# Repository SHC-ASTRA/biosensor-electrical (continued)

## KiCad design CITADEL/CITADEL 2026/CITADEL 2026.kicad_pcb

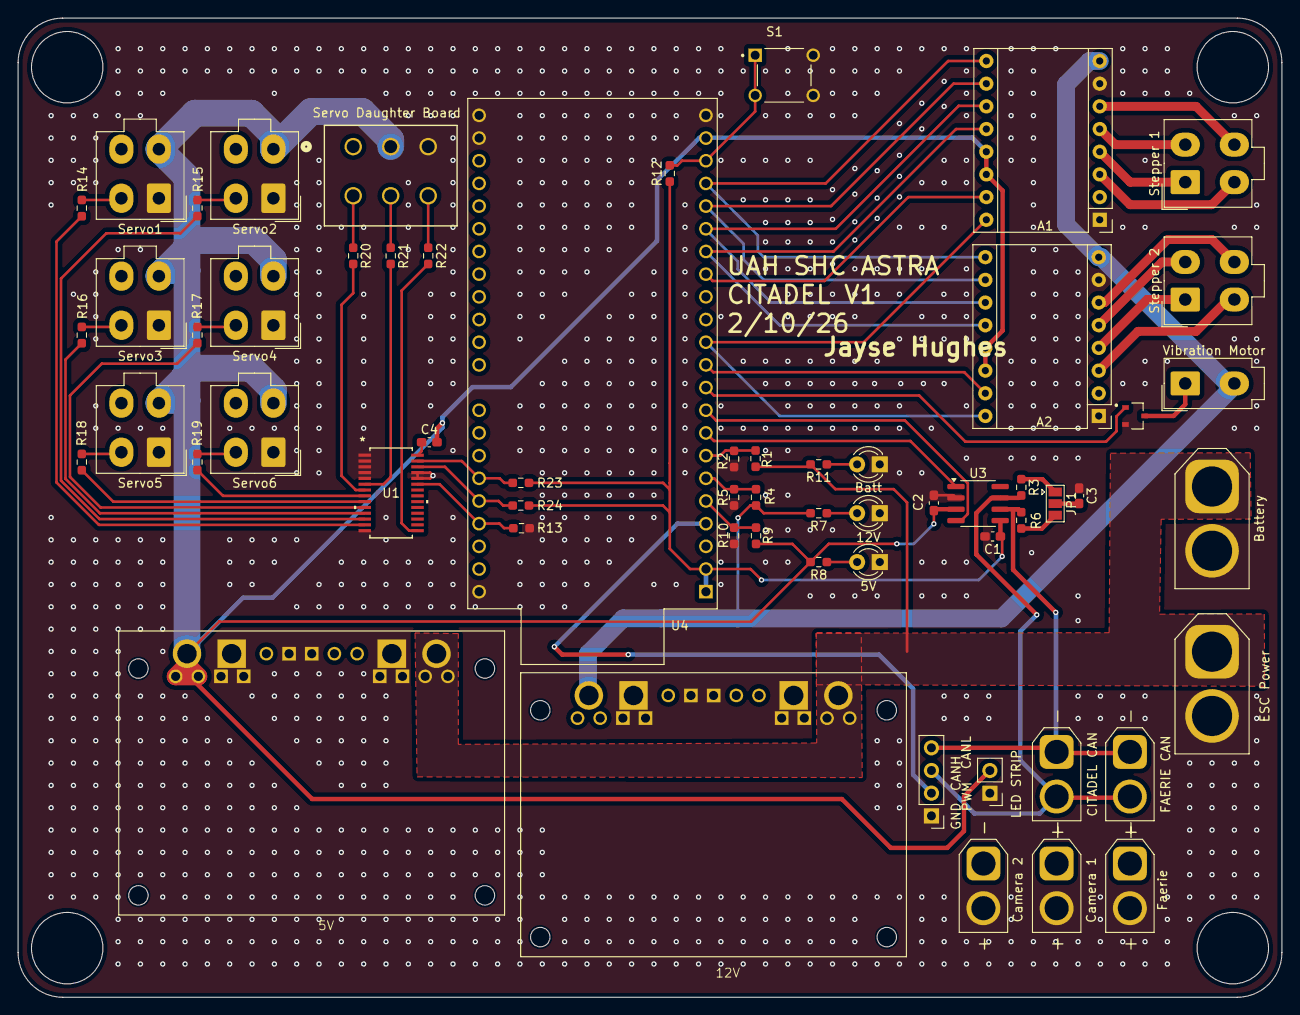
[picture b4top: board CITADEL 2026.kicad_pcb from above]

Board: 2 copper layers, 141.5 x 109.7 mm, 60 parts (0 on the bottom side), 59 nets.

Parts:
5V, 12V: LED; LED_D3.0mm
5V#2: PS1; D24V15OF5
12V#2: PS2; D24V15OF5
A1, A2: Pololu_Breakout_DRV8825; Pololu_Breakout-16_15.2x20.3mm
Batt: LED; LED_D3.0mm
Battery: Battery Connections; AMASS_XT60-M_1x02_P7.20mm_Vertical
C1, C2, C3: C; C_0603_1608Metric_Pad1.08x0.95mm_HandSolder
C4: 10uF; C_0603_1608Metric_Pad1.08x0.95mm_HandSolder
CITADEL CAN: CAN BUS; AMASS_XT30U-M_1x02_P5.0mm_Vertical
Camera 1: Camera 1; AMASS_XT30U-M_1x02_P5.0mm_Vertical
Camera 2: Camera 2; AMASS_XT30U-M_1x02_P5.0mm_Vertical
ESC Power: ESC PWR; AMASS_XT60-M_1x02_P7.20mm_Vertical
FAERIE CAN: Faerie CAN BUS; AMASS_XT30U-M_1x02_P5.0mm_Vertical
Faerie: Faerie; AMASS_XT30U-M_1x02_P5.0mm_Vertical
GND: ESC Comms; PinHeader_1x04_P2.54mm_Vertical
JP1: SolderJumper_3_Open; SolderJumper-3_P1.3mm_Open_Pad1.0x1.5mm
LED STRIP: LED Strip; PinHeader_1x02_P2.54mm_Vertical
Q7: SSM3K329R_LF; SSM3K329_LF
R1, R4, R9, R10, R12: 10 kΩ; R_0603_1608Metric_Pad0.98x0.95mm_HandSolder
R2: 2.21 kΩ; R_0603_1608Metric_Pad0.98x0.95mm_HandSolder
R3, R6: R_US; R_0603_1608Metric_Pad0.98x0.95mm_HandSolder
R5: 3.32 kΩ; R_0603_1608Metric_Pad0.98x0.95mm_HandSolder
R7, R8, R11: 1000; R_0603_1608Metric_Pad0.98x0.95mm_HandSolder
R13: 10kΩ; R_0603_1608Metric_Pad0.98x0.95mm_HandSolder
R14, R15, R16, R17, R18, R19, R20, R21, R22: 220Ω; R_0603_1608Metric_Pad0.98x0.95mm_HandSolder
R23, R24: 4.7 kΩ; R_0603_1608Metric_Pad0.98x0.95mm_HandSolder
S1: Push Button; SW_TS02-66-60-BK-100-SCR-D
Servo1: MG90S 1; Molex_Mini-Fit_Jr_5566-04A_2x02_P4.20mm_Vertical
Servo2: MG90S 2; Molex_Mini-Fit_Jr_5566-04A_2x02_P4.20mm_Vertical
Servo3: MG90S 3; Molex_Mini-Fit_Jr_5566-04A_2x02_P4.20mm_Vertical
Servo4: MG90S 4; Molex_Mini-Fit_Jr_5566-04A_2x02_P4.20mm_Vertical
Servo5: MG90S 5; Molex_Mini-Fit_Jr_5566-04A_2x02_P4.20mm_Vertical
Servo6: MG90S 6; Molex_Mini-Fit_Jr_5566-04A_2x02_P4.20mm_Vertical
Servo Daughter Board: Servo_Daughter; CONN_SD-5566-002_06_MOL
Stepper 1: Stepper 1; Molex_Mini-Fit_Jr_5566-04A_2x02_P4.20mm_Vertical
Stepper 2: Stepper 2; Molex_Mini-Fit_Jr_5566-04A_2x02_P4.20mm_Vertical
U1: PCA9685PW_118; TSSOP28_SOT361-1_NXP
U3: TJA1051T-3; SOIC-8_3.9x4.9mm_P1.27mm
U4: ESP32-S3-DEVKITC-1-N8R8
Vibration Motor: Vibration Motor; Molex_Mini-Fit_Jr_5566-02A_2x01_P4.20mm_Vertical

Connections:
+3.3V: C1.1, R12.1, R23.2, R24.2, U3.5 (VIO), U4.J1_1 (3V3), U4.J1_2 (3V3.)
+5V: 5V#2.VOUT, 5V#2.VOUT_1 (VOUT), 5V#2.VOUT_2 (VOUT), A1.13 (~RST), A1.14 (~SLP), A2.13 (~RST), A2.14 (~SLP), C2.2, C4.2, LED STRIP.2, R8.2, R9.1, Servo1.3 (+), Servo2.3 (+), Servo3.3 (+), Servo4.3 (+), Servo5.3 (+), Servo6.3 (+), Servo Daughter Board.2, U3.3 (VCC), U4.J1_21 (5V0)
+12V: 12V#2.VOUT, 12V#2.VOUT_1 (VOUT), 12V#2.VOUT_2 (VOUT), A1.8 (VMOT), A2.8 (VMOT), Camera 1.1, Camera 2.1, Faerie.1, R4.1, R7.2, Vibration Motor.2
+BATT: 5V#2.VIN, 5V#2.VIN_1 (VIN), 5V#2.VIN_2 (VIN), 12V#2.VIN, 12V#2.VIN_1 (VIN), 12V#2.VIN_2 (VIN), Battery.1, ESC Power.1, R1.1, R11.2
/5V_ADC: R9.2, R10.1, U4.J1_5 (GPIO5)
/12V_ADC: R4.2, R5.1, U4.J1_6 (GPIO6)
/BATT_ADC: R1.2, R2.1, U4.J1_7 (GPIO7)
/Button: R12.2, S1.1, S1.3, U4.J1_20 (GPIO14)
/CIT_CAN+: CITADEL CAN.2, FAERIE CAN.2, GND.3, R3.2, U3.7 (CANH)
/CIT_CAN-: CITADEL CAN.1, FAERIE CAN.1, GND.4, R6.2, U3.6 (CANL)
/CRX_ESP: U3.4 (RXD), U4.J1_9 (GPIO16)
/CTX_ESP: U3.1 (TXD), U4.J1_8 (GPIO15)
/ESC_PWM: GND.2, U4.J1_4 (GPIO4)
/Motor1_1: A1.4 (A1), Stepper 1.1
/Motor1_2: A1.3 (A2), Stepper 1.3
/Motor1_3: A1.5 (B1), Stepper 1.2
/Motor1_4: A1.6 (B2), Stepper 1.4
/Motor2_1: A2.4 (A1), Stepper 2.1
/Motor2_2: A2.3 (A2), Stepper 2.3
/Motor2_3: A2.5 (B1), Stepper 2.2
/Motor2_4: A2.6 (B2), Stepper 2.4
/SCL: R24.1, U1.26 (SCL), U4.J3_5 (GPIO2)
/SDA: R23.1, U1.27 (SDA), U4.J3_6 (MTMS/GPIO42)
/Servo1: R14.1, Servo1.2 (PWM)
/Servo2: R15.1, Servo2.2 (PWM)
/Servo3: R16.1, Servo3.2 (PWM)
/Servo4: R17.1, Servo4.2 (PWM)
/Servo5: R18.1, Servo5.2 (PWM)
/Servo6: R19.1, Servo6.2 (PWM)
/Servo7: R20.1, Servo Daughter Board.4
/Servo8: R21.1, Servo Daughter Board.5
/Servo9: R22.2, Servo Daughter Board.6
/Servo_Enable_Output: R13.1, U1.23 (*OE), U4.J3_4 (GPIO1)
/Stepper1_STEP: A1.15 (STEP), U4.J1_15 (GPIO9)
/Stepper2_STEP: A2.15 (STEP), U4.J1_11 (GPIO18)
/Stepper_DIR: A1.16 (DIR), A2.16 (DIR), U4.J1_12 (GPIO8)
/Stepper_EN: A1.9 (~EN), A2.9 (~EN), U4.J1_19 (GPIO13)
/Stepper_M0: A1.10 (M0), A2.10 (M0), U4.J1_18 (GPIO12)
/Stepper_M1: A1.11 (M1), A2.11 (M1), U4.J1_17 (GPIO11)
/Stepper_M2: A1.12 (M2), A2.12 (M2), U4.J1_16 (GPIO10)
/VibMotorMOS: Q7.3, Vibration Motor.1
/VibMotorSignal: Q7.1, U4.J1_10 (GPIO17)
GND: 5V.1 (K), 5V#2.GND, 5V#2.GND1 (GND), 5V#2.GND2 (GND), 5V#2.GND3 (GND), 5V#2.GND4 (GND), 5V#2.GND5 (GND), 5V#2.GND6 (GND), 5V#2.GND7 (GND), 12V.1 (K), 12V#2.GND, 12V#2.GND1 (GND), 12V#2.GND2 (GND), 12V#2.GND3 (GND), 12V#2.GND4 (GND), 12V#2.GND5 (GND), 12V#2.GND6 (GND), 12V#2.GND7 (GND), A1.1 (GND), A1.7 (GND), A2.1 (GND), A2.7 (GND), Batt.1 (K), Battery.2, C1.2, C2.1, C3.1, Camera 1.2, Camera 2.2, ESC Power.2, Faerie.2, GND.1, LED STRIP.1, Q7.2, R2.2, R5.2, R10.2, R13.2, S1.2, S1.4, Servo1.1 (-), Servo2.1 (-), Servo3.1 (-), Servo4.1 (-), Servo5.1 (-), Servo6.1 (-), Servo Daughter Board.3, U1.1 (A0), U1.2 (A1), U1.3 (A2), U1.4 (A3), U1.5 (A4), U1.14 (VSS), U1.24 (A5), U1.25 (EXTCLK), U3.2 (GND), U4.J1_22 (GND3), U4.J3_1 (GND), U4.J3_21 (GND1), U4.J3_22 (GND2)
unnamed: Batt.2 (A), R11.1
unnamed: 12V.2 (A), R7.1
unnamed: 5V.2 (A), R8.1
unnamed: JP1.3 (A), R6.1
unnamed: JP1.1 (B), R3.1
unnamed: C3.2, JP1.2 (C)
unnamed: R21.2, U1.6 (LED0)
unnamed: R20.2, U1.7 (LED1)
unnamed: R19.2, U1.8 (LED2)
unnamed: R18.2, U1.9 (LED3)
unnamed: R17.2, U1.10 (LED4)
unnamed: R16.2, U1.11 (LED5)
unnamed: R15.2, U1.12 (LED6)
unnamed: R14.2, U1.13 (LED7)
unnamed: R22.1, U1.15 (LED8)
unnamed: C4.1, U1.28 (VDD)

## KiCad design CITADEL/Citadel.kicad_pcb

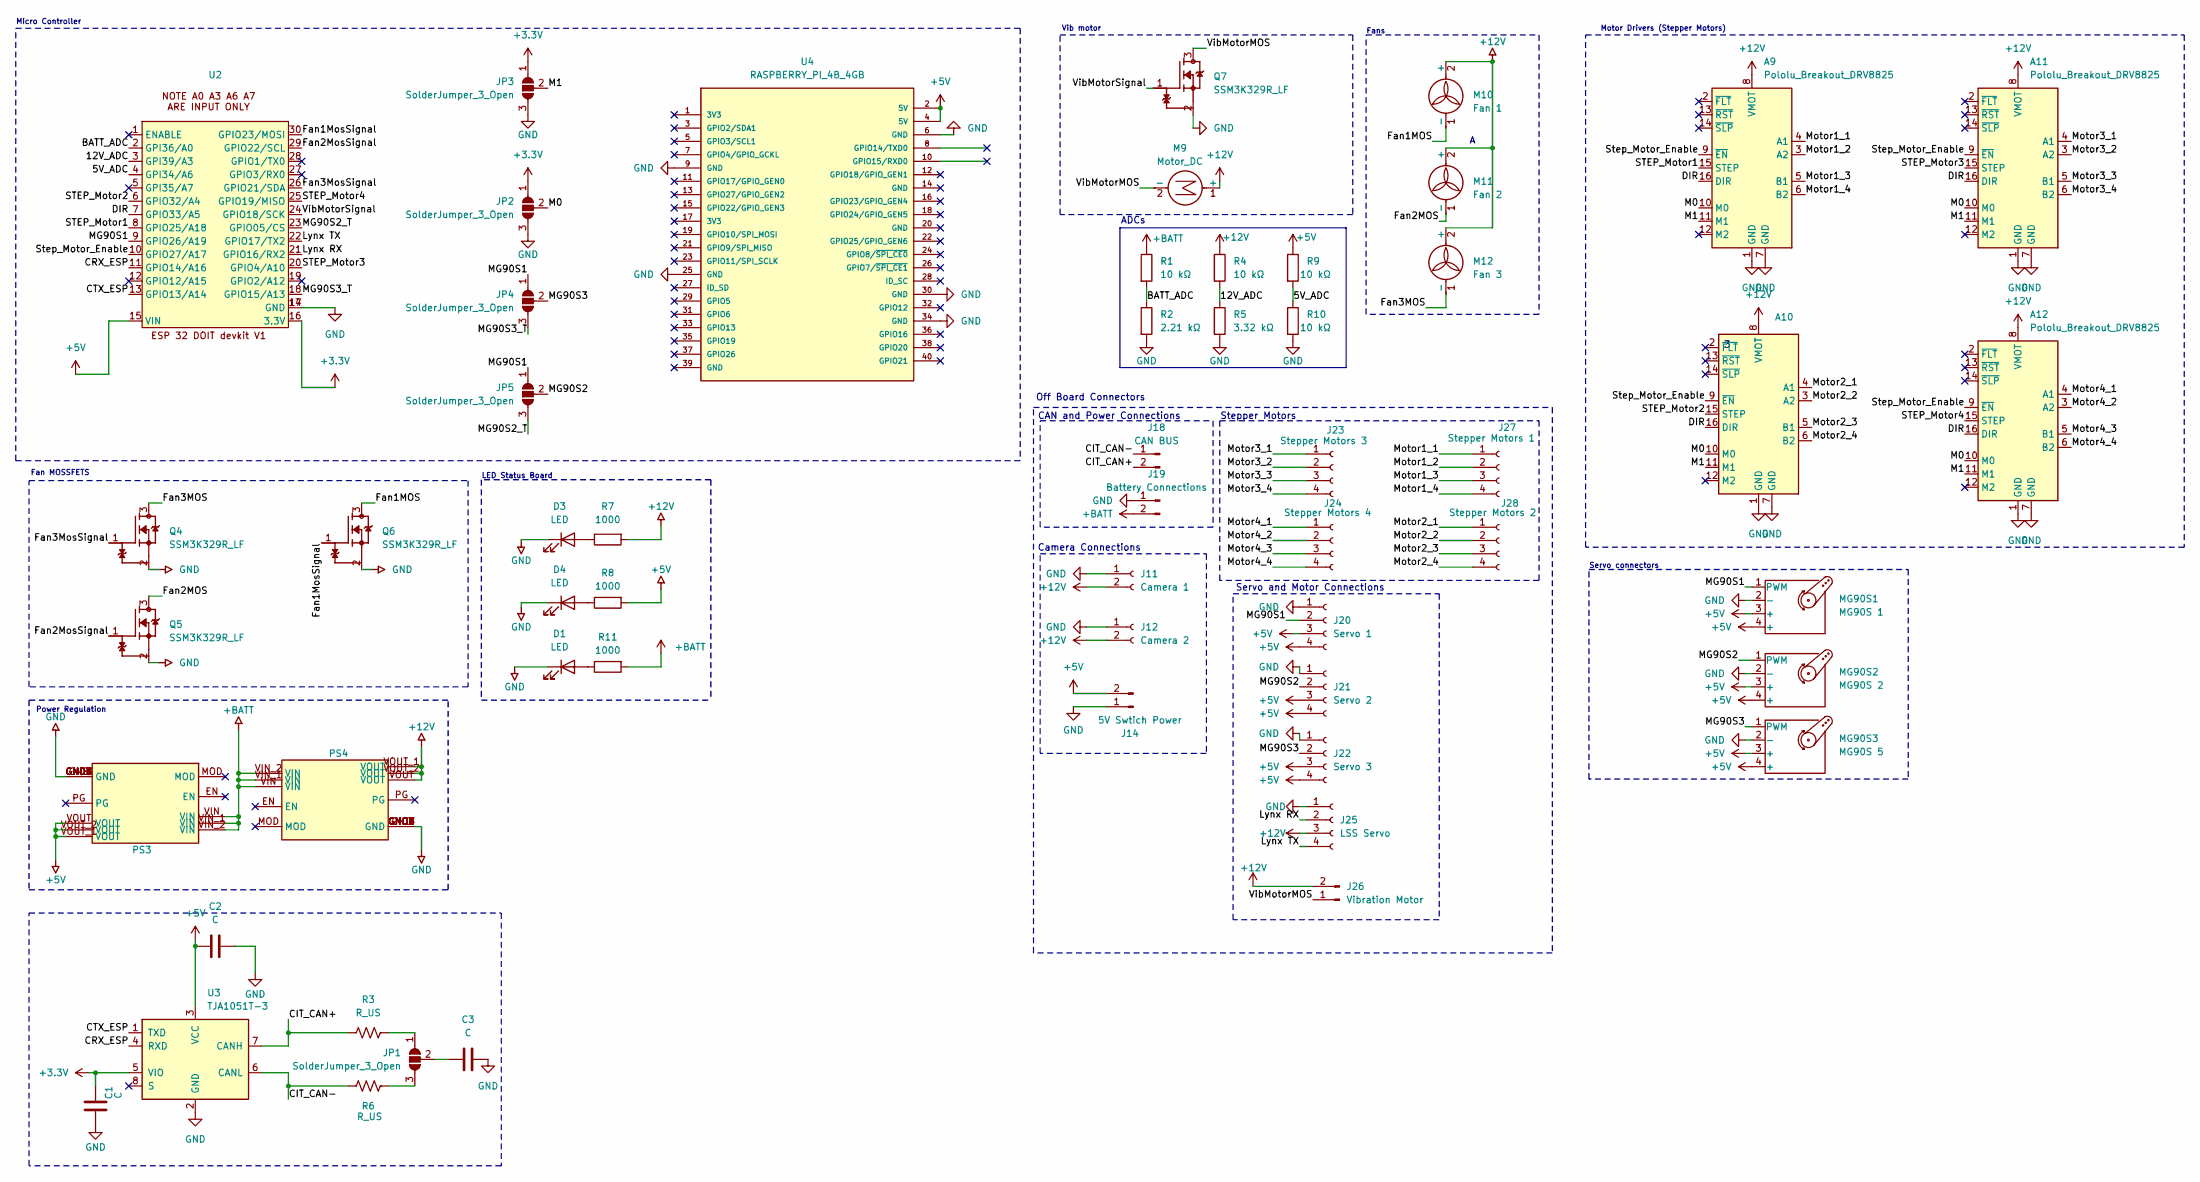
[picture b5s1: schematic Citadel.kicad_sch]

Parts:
A9, A10, A11, A12: Pololu_Breakout_DRV8825; Pololu_Breakout-16_15.2x20.3mm
C1, C2, C3: C; C_0603_1608Metric_Pad1.08x0.95mm_HandSolder
D1, D3, D4: LED; LED_D3.0mm
J11: Camera 1; AMASS_XT30U-F_1x02_P5.0mm_Vertical
J12: Camera 2; AMASS_XT30U-F_1x02_P5.0mm_Vertical
J14: 5V Swtich Power; Molex_Mini-Fit_Jr_5566-02A_2x01_P4.20mm_Vertical
J18: CAN BUS; AMASS_XT30U-F_1x02_P5.0mm_Vertical
J19: Battery Connections; AMASS_XT60-M_1x02_P7.20mm_Vertical
J20: Servo 1; Molex_Mini-Fit_Jr_5566-04A_2x02_P4.20mm_Vertical
J21: Servo 2; Molex_Mini-Fit_Jr_5566-04A_2x02_P4.20mm_Vertical
J22: Servo 3; Molex_Mini-Fit_Jr_5566-04A_2x02_P4.20mm_Vertical
J23: Stepper Motors 3; Molex_Mini-Fit_Jr_5566-04A_2x02_P4.20mm_Vertical
J24: Stepper Motors 4; Molex_Mini-Fit_Jr_5566-04A_2x02_P4.20mm_Vertical
J25: LSS Servo; Molex_Mini-Fit_Jr_5566-04A_2x02_P4.20mm_Vertical
J26: Vibration Motor; Molex_Mini-Fit_Jr_5566-02A_2x01_P4.20mm_Vertical
J27: Stepper Motors 1; Molex_Mini-Fit_Jr_5566-04A_2x02_P4.20mm_Vertical
J28: Stepper Motors 2; Molex_Mini-Fit_Jr_5566-04A_2x02_P4.20mm_Vertical
JP1, JP2, JP3, JP4, JP5: SolderJumper_3_Open; SolderJumper-3_P1.3mm_Open_Pad1.0x1.5mm
M9: Motor_DC
M10: Fan 1; Molex_Mini-Fit_Jr_5566-02A_2x01_P4.20mm_Vertical
M11: Fan 2; Molex_Mini-Fit_Jr_5566-02A_2x01_P4.20mm_Vertical
M12: Fan 3; Molex_Mini-Fit_Jr_5566-02A_2x01_P4.20mm_Vertical
MG90S1: MG90S 1
MG90S2: MG90S 2
MG90S3: MG90S 5
PS3, PS4: D24V15OF5
Q4, Q5, Q6, Q7: SSM3K329R_LF; SSM3K329_LF; PARTREV 1.0
R1, R4, R9, R10: 10 kΩ; R_0603_1608Metric_Pad0.98x0.95mm_HandSolder
R2: 2.21 kΩ; R_0603_1608Metric_Pad0.98x0.95mm_HandSolder
R3, R6: R_US; R_0603_1608Metric_Pad0.98x0.95mm_HandSolder
R5: 3.32 kΩ; R_0603_1608Metric_Pad0.98x0.95mm_HandSolder
R7, R8, R11: 1000; R_0603_1608Metric_Pad0.98x0.95mm_HandSolder
U2: esp32_devkit_v1
U3: TJA1051T-3; SOIC-8_3.9x4.9mm_P1.27mm
U4: RASPBERRY_PI_4B_4GB; MODULE_RASPBERRY_PI_4B_4GB

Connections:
+3.3V: C1.1, JP2.1 (B), JP3.1 (B), U2.16 (3.3V), U3.5 (VIO)
+5V: C2.2, J14.2, J20.3, J20.4, J21.3, J21.4, J22.3, J22.4, MG90S1.3 (+), MG90S1.4 (+), MG90S2.3 (+), MG90S2.4 (+), MG90S3.3 (+), MG90S3.4 (+), PS3.VOUT, PS3.VOUT_1 (VOUT), PS3.VOUT_2 (VOUT), R8.2, R9.1, U2.15 (VIN), U3.3 (VCC), U4.2 (5V), U4.4 (5V)
+12V: A9.8 (VMOT), A10.8 (VMOT), A11.8 (VMOT), A12.8 (VMOT), J11.2, J12.2, J25.3, J26.2, M9.1 (+), M10.2 (+), M11.2 (+), M12.2 (+), PS4.VOUT, PS4.VOUT_1 (VOUT), PS4.VOUT_2 (VOUT), R4.1, R7.2
+BATT: J19.2, PS3.VIN, PS3.VIN_1 (VIN), PS3.VIN_2 (VIN), PS4.VIN, PS4.VIN_1 (VIN), PS4.VIN_2 (VIN), R1.1, R11.2
/5V_ADC: R9.2, R10.1, U2.4 (GPI34/A6)
/12V_ADC: R4.2, R5.1, U2.3 (GPI39/A3)
/BATT_ADC: R1.2, R2.1, U2.2 (GPI36/A0)
/CIT_CAN+: J18.2, R3.2, U3.7 (CANH)
/CIT_CAN-: J18.1, R6.2, U3.6 (CANL)
/CRX_ESP: U2.11 (GPIO14/A16), U3.4 (RXD)
/CTX_ESP: U2.13 (GPIO13/A14), U3.1 (TXD)
/DIR: A9.16 (DIR), A10.16 (DIR), A11.16 (DIR), A12.16 (DIR), U2.7 (GPIO33/A5)
/Fan1MOS: M10.1 (-), Q6.3
/Fan1MosSignal: Q6.1, U2.30 (GPIO23/MOSI)
/Fan2MOS: M11.1 (-), Q5.3
/Fan2MosSignal: Q5.1, U2.29 (GPIO22/SCL)
/Fan3MOS: M12.1 (-), Q4.3
/Fan3MosSignal: Q4.1, U2.26 (GPIO21/SDA)
/Lynx RX: J25.2, U2.21 (GPIO16/RX2)
/Lynx TX: J25.4, U2.22 (GPIO17/TX2)
/M0: A9.10 (M0), A10.10 (M0), A11.10 (M0), A12.10 (M0), JP2.2 (C)
/M1: A9.11 (M1), A10.11 (M1), A11.11 (M1), A12.11 (M1), JP3.2 (C)
/MG90S1: J20.2, JP4.1 (B), JP5.1 (B), MG90S1.1 (PWM), U2.9 (GPIO26/A19)
/MG90S2: J21.2, JP5.2 (C), MG90S2.1 (PWM)
/MG90S2_T: JP5.3 (A), U2.23 (GPIO05/CS)
/MG90S3: J22.2, JP4.2 (C), MG90S3.1 (PWM)
/MG90S3_T: JP4.3 (A), U2.18 (GPIO15/A13)
/Motor1_1: A9.4 (A1), J27.1
/Motor1_2: A9.3 (A2), J27.2
/Motor1_3: A9.5 (B1), J27.3
/Motor1_4: A9.6 (B2), J27.4
/Motor2_1: A10.4 (A1), J28.1
/Motor2_2: A10.3 (A2), J28.2
/Motor2_3: A10.5 (B1), J28.3
/Motor2_4: A10.6 (B2), J28.4
/Motor3_1: A11.4 (A1), J23.1
/Motor3_2: A11.3 (A2), J23.2
/Motor3_3: A11.5 (B1), J23.3
/Motor3_4: A11.6 (B2), J23.4
/Motor4_1: A12.4 (A1), J24.1
/Motor4_2: A12.3 (A2), J24.2
/Motor4_3: A12.5 (B1), J24.3
/Motor4_4: A12.6 (B2), J24.4
/STEP_Motor1: A9.15 (STEP), U2.8 (GPIO25/A18)
/STEP_Motor2: A10.15 (STEP), U2.6 (GPIO32/A4)
/STEP_Motor3: A11.15 (STEP), U2.20 (GPIO4/A10)
/STEP_Motor4: A12.15 (STEP), U2.25 (GPIO19/MISO)
/Step_Motor_Enable: A9.9 (~EN), A10.9 (~EN), A11.9 (~EN), A12.9 (~EN), U2.10 (GPIO27/A17)
/VibMotorMOS: J26.1, M9.2 (-), Q7.3
/VibMotorSignal: Q7.1, U2.24 (GPIO18/SCK)
GND: A9.1 (GND), A9.7 (GND), A10.1 (GND), A10.7 (GND), A11.1 (GND), A11.7 (GND), A12.1 (GND), A12.7 (GND), C1.2, C2.1, C3.1, D1.1 (K), D3.1 (K), D4.1 (K), J11.1, J12.1, J14.1, J19.1, J20.1, J21.1, J22.1, J25.1, JP2.3 (A), JP3.3 (A), MG90S1.2 (-), MG90S2.2 (-), MG90S3.2 (-), PS3.GND, PS3.GND1 (GND), PS3.GND2 (GND), PS3.GND3 (GND), PS3.GND4 (GND), PS3.GND5 (GND), PS3.GND6 (GND), PS3.GND7 (GND), PS4.GND, PS4.GND1 (GND), PS4.GND2 (GND), PS4.GND3 (GND), PS4.GND4 (GND), PS4.GND5 (GND), PS4.GND6 (GND), PS4.GND7 (GND), Q4.2, Q5.2, Q6.2, Q7.2, R2.2, R5.2, R10.2, U2.14 (GND), U2.17 (GND), U3.2 (GND), U4.6 (GND), U4.9 (GND), U4.25 (GND), U4.30 (GND), U4.34 (GND)
unnamed: D1.2 (A), R11.1
unnamed: D3.2 (A), R7.1
unnamed: D4.2 (A), R8.1
unnamed: JP1.3 (A), R6.1
unnamed: JP1.1 (B), R3.1
unnamed: C3.2, JP1.2 (C)

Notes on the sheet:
Motor Drivers (Stepper Motors)
Camera Connections
Servo connectors
Off Board Connectors
ADCs
Power Regulation
CAN and Power Connections
Servo and Motor Connections
Stepper Motors
LED Status Board
Micro Controller
Fan MOSSFETS
Vib motor
Fans

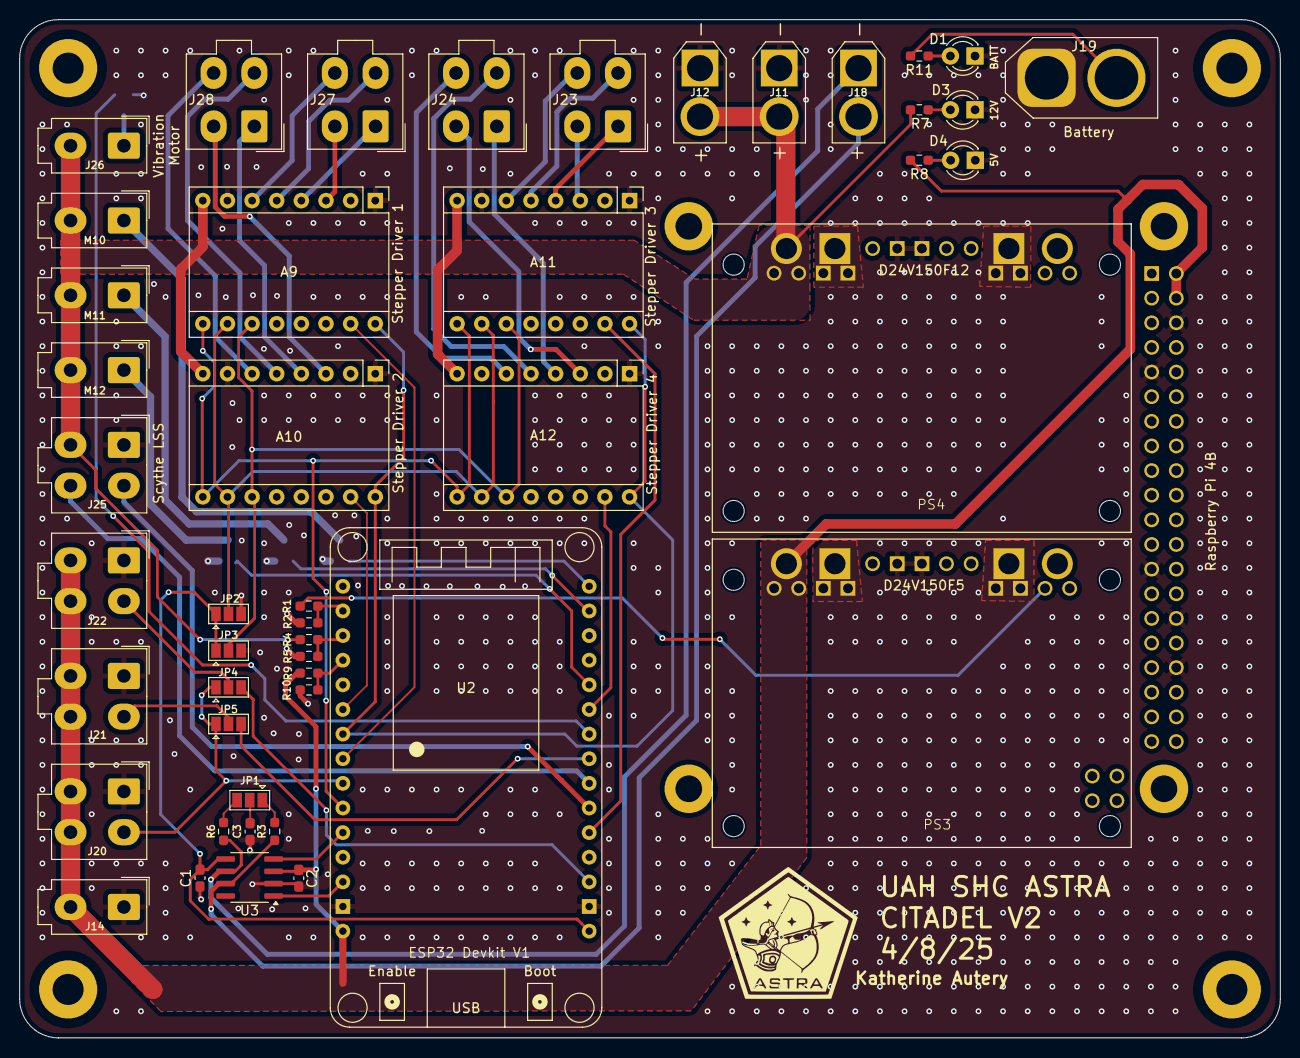
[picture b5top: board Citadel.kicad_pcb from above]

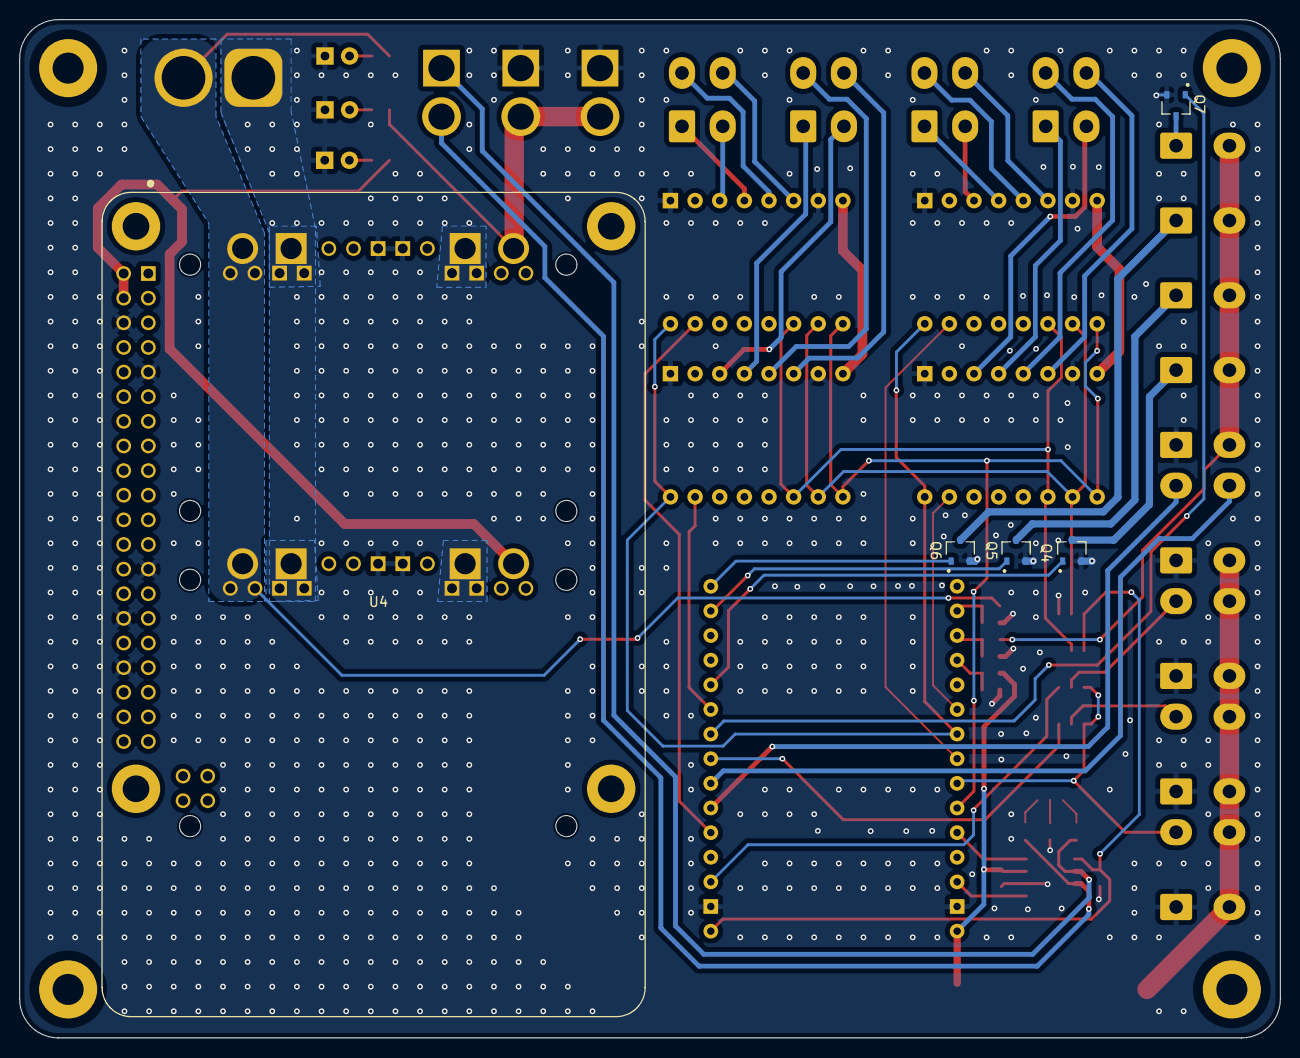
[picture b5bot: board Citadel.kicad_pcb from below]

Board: 2 copper layers, 130.0 x 105.0 mm, 52 parts (4 on the bottom side), 57 nets.

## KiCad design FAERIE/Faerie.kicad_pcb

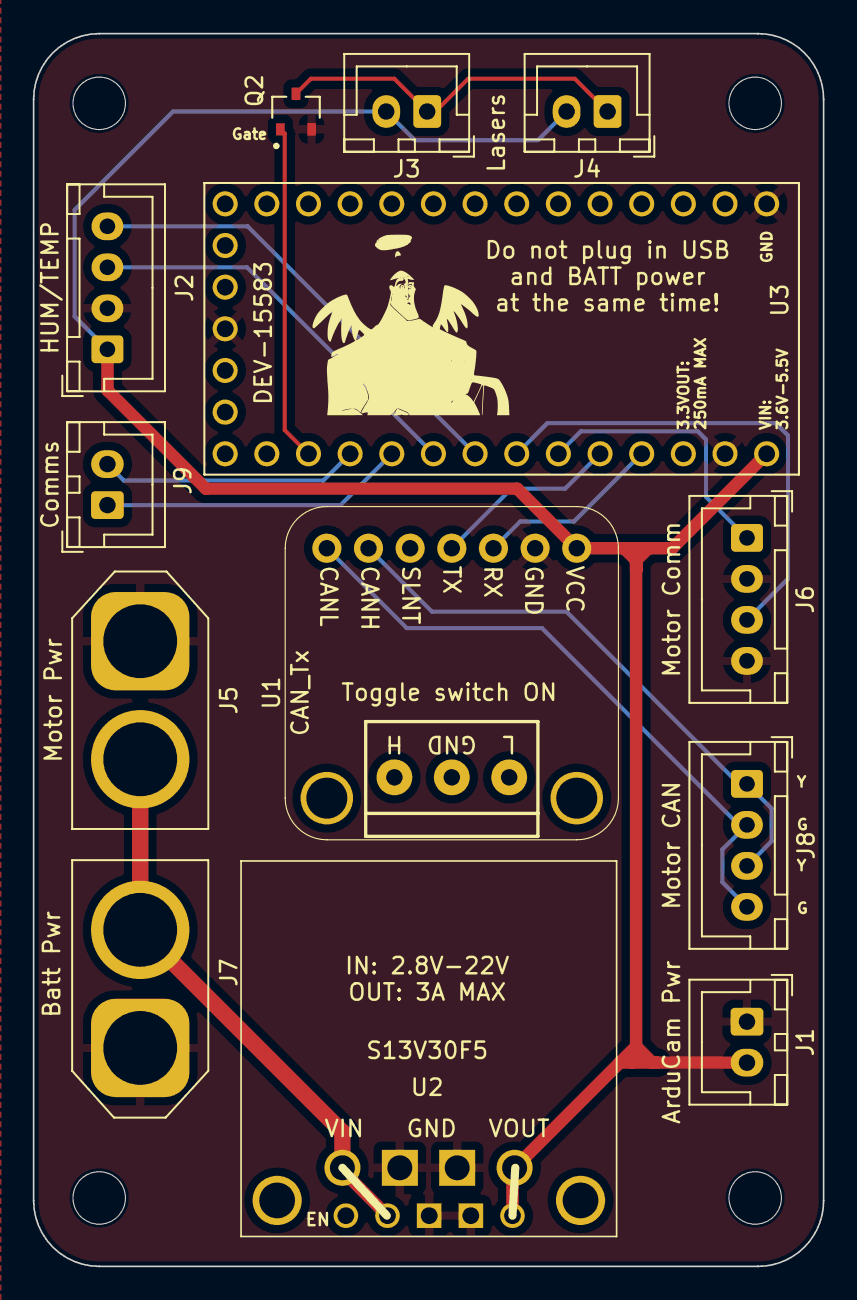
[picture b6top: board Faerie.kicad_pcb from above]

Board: 2 copper layers, 48.2 x 75.2 mm, 13 parts (0 on the bottom side), 15 nets.

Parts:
J1: ArduCam Pwr; JST_XH_B2B-XH-A_1x02_P2.50mm_Vertical
J2: HUM/TEMP; JST_XH_B4B-XH-A_1x04_P2.50mm_Vertical
J3: Laser 1 Conn; JST_XH_B2B-XH-A_1x02_P2.50mm_Vertical
J4: Laser 2 Conn; JST_XH_B2B-XH-A_1x02_P2.50mm_Vertical
J5: Motor Pwr; AMASS_XT60-F_1x02_P7.20mm_Vertical
J6: Motor Comm; JST_XH_B4B-XH-A_1x04_P2.50mm_Vertical
J7: Batt Pwr; AMASS_XT60-F_1x02_P7.20mm_Vertical
J8: Motor CAN; JST_XH_B4B-XH-A_1x04_P2.50mm_Vertical
J9: Comms; JST_XH_B2B-XH-A_1x02_P2.50mm_Vertical
Q2: SSM3K329R_LF; SOTFL95P240X88-3N
U1: CAN_Tx; CanTX
U2: S13V30F5
U3: DEV-15583; MODULE_DEV-15583

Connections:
+5V: J1.2, J2.1, J3.2, J4.2, U1.7 (VCC), U2.3 (Vout), U3.VIN
+BATT: J5.2, J7.2, U2.1 (Vin)
/CANH: J8.1, J8.3, U1.2 (CANH)
/CANL: J8.2, J8.4, U1.1 (CANL)
/CRX: U1.5 (RX), U3.23
/CTX: U1.4 (TX), U3.22
/LGate: Q2.1, U3.15
/M_PWM1: J6.1, U3.21
/M_PWM2: J6.3, U3.20
/RX: J9.1, U3.17
/SCL: J2.4, U3.19
/SDA: J2.3, U3.18
/TX: J9.2, U3.16
GND: J1.1, J2.2, J5.1, J6.2, J6.4, J7.1, Q2.2, U1.6 (GND), U2.2 (GND), U3.G1, U3.G2, U3.G3
unnamed: J3.1, J4.1, Q2.3
